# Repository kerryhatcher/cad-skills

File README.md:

# cad-skills

Agent skills for CAD work. You can install them with the [`skills`](https://skills.sh) CLI into Claude Code, Codex, Cursor, OpenCode and [many other agents](https://github.com/vercel-labs/skills/blob/main/docs/agents.md).

## Skills

| Skill | Function |
|---|---|
| [`cadquery`](skills/cadquery/SKILL.md) | Make parametric 3D CAD models in Python with [CadQuery](https://cadquery.readthedocs.io/). It includes parts, sketches, assemblies and export to STEP, STL, 3MF, DXF, SVG and glTF. Its tools examine, measure and render models. Thus the agent can make sure that its work is correct. All Python runs with `uv`. |
| [`structural-analysis`](skills/structural-analysis/SKILL.md) | Find if a part is sufficiently strong for its task. It does a linear static FEA (gmsh and scikit-fem, quadratic tetrahedra) of CadQuery or STEP models. It calculates safety factors with data for **printed** Prusament and Jessie materials. It also examines the layer adhesion for the print orientation. It renders the boundary conditions and the stress to PNG files, and exports VTU files for ParaView. |
| [`print-prep`](skills/print-prep/SKILL.md) | Prepare a model for FDM printing. It examines the mesh. It makes sure that the part is not too large for the build volume. It compares print orientations and puts them in sequence from best to worst. It compares the supports, the area on the bed, the risk that the part falls, and the load across the layers. It also examines the wall thickness and exports the turned model as 3MF or STL. It includes design rules for FDM on the Prusa MK4. |
| [`prusaslicer`](skills/prusaslicer/SKILL.md) | Slice with PrusaSlicer, with no GUI. It uses the Prusa profiles for the MK4 and MK4S, which include Prusament and Jessie filaments. You can change the settings that give strength. It makes sure that the G-code is for the correct printer, nozzle and temperatures. It shows the time, the filament and the slicer warnings. It can read `.bgcode` files. |

For a printed part, use these four skills in this sequence:

1. **Model** the part (`cadquery`).
2. **Turn and examine** the part for printing (`print-prep`).
3. **Calculate the strength** with the same build direction (`structural-analysis`).
4. **Slice** the part (`prusaslicer`).

The repository also contains three PCB skills:

| Skill | Function |
|---|---|
| [`pcb-design`](skills/pcb-design/SKILL.md) | Edit KiCad projects, compare schematic and board identities, run design checks, and measure the supported mechanical fixture. |
| [`pcb-fab-package`](skills/pcb-fab-package/SKILL.md) | Compare fabrication outputs with a supplier profile and make a package with bound evidence. It includes OSH Park setup guidance. |
| [`pcba-design`](skills/pcba-design/SKILL.md) | Apply variants and alternate approvals, make a BOM, compare stock, and make Sierra draft artifacts and an assembly package. |

The KiCad tool operations use a local image whose identity matches the project toolchain lock.
The skill guides state the supported geometry, source setup, commands and qualification limits.
A package with status `unqualified` does not establish supplier acceptance or a physical test result.

## How to install the skills

### Claude Code plugin

This repository is a Claude Code plugin marketplace. It supplies the plugin `cad-skills` with all seven skills.

```
/plugin marketplace add kerryhatcher/cad-skills
/plugin install cad-skills@cad-skills
```

The plugin has a `SessionStart` hook. The hook tells the agent the path of the plugin.
Thus the agent can resolve the script paths, such as `skills/cadquery/scripts/inspect_model.py`, in the skill documents.
The plugin is in `plugins/cad-skills`. Its `skills` link points to the `skills` directory of the repository.

### Other agents

```bash
# this project (select the agents in a menu)
npx skills add kerryhatcher/cad-skills

# one skill, one agent, for all projects
npx skills add kerryhatcher/cad-skills --skill cadquery -a claude-code -g

# show the contents of the repository
npx skills add kerryhatcher/cad-skills --list
```

The computer that runs the agent must have:

- [uv](https://docs.astral.sh/uv/). It downloads CadQuery when necessary. It is not necessary to install CadQuery.
- Node.js (minimum version 22.20), for the `skills` CLI.
- [PrusaSlicer](https://www.prusa3d.com/page/prusaslicer_424/) (minimum version 2.8), for the `prusaslicer` skill only. On Linux: `flatpak install flathub com.prusa3d.PrusaSlicer`.

## Contents of `cadquery`

```
skills/cadquery/
├── SKILL.md                    # procedure, mental model, quick reference, frequent mistakes
├── references/                 # the agent reads these when necessary
│   ├── workplane.md            # fluent API: workplanes, 2D, 3D operations, patterns, tags
│   ├── selectors.md            # selection of faces, edges and vertices
│   ├── sketch.md               # cq.Sketch: profiles from faces, edges or constraints
│   ├── assemblies.md           # Assembly, Location, constraints, colors
│   ├── free-func.md            # cadquery.func, Shape API, Vector/Plane/Location
│   ├── import-export.md        # formats, units, mesh tolerance, imports
│   ├── recipes.md              # 12 tested examples
│   ├── design-guidelines.md    # general rules for FDM, CNC, laser and sheet metal
│   └── troubleshooting.md      # error message → cause → repair
├── scripts/
│   ├── inspect_model.py        # build, validate, measure, export and render PNG views
│   └── cq_api.py               # signatures and docstrings of the installed CadQuery
└── templates/
    ├── part.py                 # start file for a parametric part (PEP 723)
    └── assembly.py             # start file for a parametric assembly (PEP 723)
```

The scripts have [PEP 723](https://peps.python.org/pep-0723/) headers. Thus they run on all computers with `uv run`:

```bash
uv run skills/cadquery/scripts/inspect_model.py my_part.py --png out/preview.png --views -o out/my_part.step
uv run skills/cadquery/scripts/cq_api.py Workplane.cboreHole
```

`inspect_model.py` does these tasks:

- It shows if the model is correct. It also shows the number of solids, the bounding box, the volume and the center of mass.
- It changes top-level parameters (`--set width=50`).
- It finds interference in an assembly (`--interference`).
- It exports to all supported formats (`-o`).
- It renders PNG views (iso, front, top, right) with no screen. An agent that can read images can examine these views.

## Example: from a model to a print

```bash
# 1. orientation and printability (shows the build direction for the FEA)
uv run skills/print-prep/scripts/printability.py bracket.py --load-axis z --png out/orient.png -o out/bracket.3mf
# 2. can the part hold 100 N in this orientation?
uv run skills/structural-analysis/scripts/fea.py bracket.py --material jessie-petg \
    --fix "face:7" --force "face:5=0,0,-100" --build-dir y --sf-target 3 --png out/fea.png
# 3. slice for an MK4 with settings for strength
uv run skills/prusaslicer/scripts/slice.py slice out/bracket.3mf --printer MK4 \
    --filament "Jessie PETG" --perimeters 5 --infill 40% -o out/bracket.bgcode
```

## Tests

The test script runs each ```` ```python ```` code block in the Markdown files of the skills. It uses the CadQuery version that `uv` installs:

```bash
uv run tests/test_snippets.py          # all blocks
uv run tests/test_snippets.py -k recipes -v
```

If a code block cannot run without other code, put `# notest: <reason>` on its first line. A mark with no reason fails the test.

The FEA, printability and slicer tools have regression tests:

- The FEA results agree with beam theory.
- The profile resolution agrees with the Prusa profile bundle.
- If the computer has PrusaSlicer, a test slices a model.

```bash
uv run tests/test_print_tools.py
```

The record contracts in `contracts/` have their own tests:

```bash
uv run tests/test_pcb_tools.py
uv run tests/test_project_io.py
uv run tests/test_skill_packages.py
uv run tests/test_snippets.py --dry-run   # show the environment of each block
```

CI runs these test scripts each time that you push commits (`.github/workflows/test.yml`).

### Language

Write all documentation, code comments, help text, commit messages and agent messages in ASD-STE100 Simplified Technical English (STE). `AGENTS.md` gives the rules and examples. `CLAUDE.md` imports `AGENTS.md` for Claude Code.

## Local release checks

These commands run without a model provider:

```bash
uv run tests/test_release_packaging.py
uv run tests/test_release_harness.py
uv run tests/test_release_isolation.py
uv run tests/test_artifact_fixtures.py
uv run tests/test_artifact_expectations.py
```

The packaging suite examines the source manifests and distribution exclusions.
The harness uses local stubs. The isolation suite measures the supported local filesystem and network boundary.
The artifact suites compare retained fixture results and altered temporary copies with explicit expectations.
These results do not establish the authenticated host route or live-provider behavior.
Provider authorization remains zero. The artifact evaluations remain held.

Supplier pages and documents remain local evidence. Distribution excludes their full copies.
The fabrication skill has a separate source setup command. Its guide states the hash and source-review rules.
See [the licensing record](docs/release-licensing.md) for third-party content and distribution decisions.

## License

MIT

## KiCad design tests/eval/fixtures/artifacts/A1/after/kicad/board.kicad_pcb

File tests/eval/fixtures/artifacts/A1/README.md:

# A1: pcb-design value edit (ready)

This fixture holds an owned copy of the accepted RC bare board. It records one design edit: R2 changes from 10k to 20k.

- `before/`: the accepted template `skills/pcb-design/templates/rc-bare-board`, unchanged.
- `after/`: the same project after the edit. The schematic and the board hold 20k. The interface names the edited board.
- `after/expect/r2-value.json`: the expected difference. The author wrote it before the edit.
- `after/out/`: the measured results of the tool commands. The history folder holds the prior board.
- `after/README.md`: the template README, unchanged. It still states R2 = 10 kohm and 2.086 V. This file states the values for R2 = 20 kohm.
- `after/simulations/`: the simulation circuit and its assertion. Both model R2 = 20k.

Procedure, in order:

1. Write the expected difference before the edit.
2. Change the Value of R2 on line 980 of `kicad/board.kicad_sch`. No other line changes.
3. Run `erc`. It passes with zero findings.
4. Run `update --adapter gui --expect expect/r2-value.json`. It passes on the measured image ID `b2731833711a`.
5. Run `interface --apply`. The tool rebinds the interface to the saved board and writes the hash. The author does not edit the hash.
6. Run `drc`. It passes. Run `erc` again, because the board changed. It passes.
7. Run `sim`. It measures 1.298448 V.
8. Run `check --for ready`. It exits 0 and reports `ready`.

The simulation values differ from the template. The template assertion of 2.086 V belongs to R2 = 10k. For R2 = 20k, the author computed the expected value as 3.3 V times (1 minus e to the power of minus 0.5). The result is 1.29845 V. The assertion is 1.298 V, with the template tolerance of 1 percent (0.01298 V).

The focused test `tests/test_artifact_fixtures.py` checks these facts from the repository files. It starts no container and no KiCad process.

Limits: one measured GUI dialog layout, KiCad 10.0.5, the local image only. No supplier record is bound. No provider call. No real HOME is used.

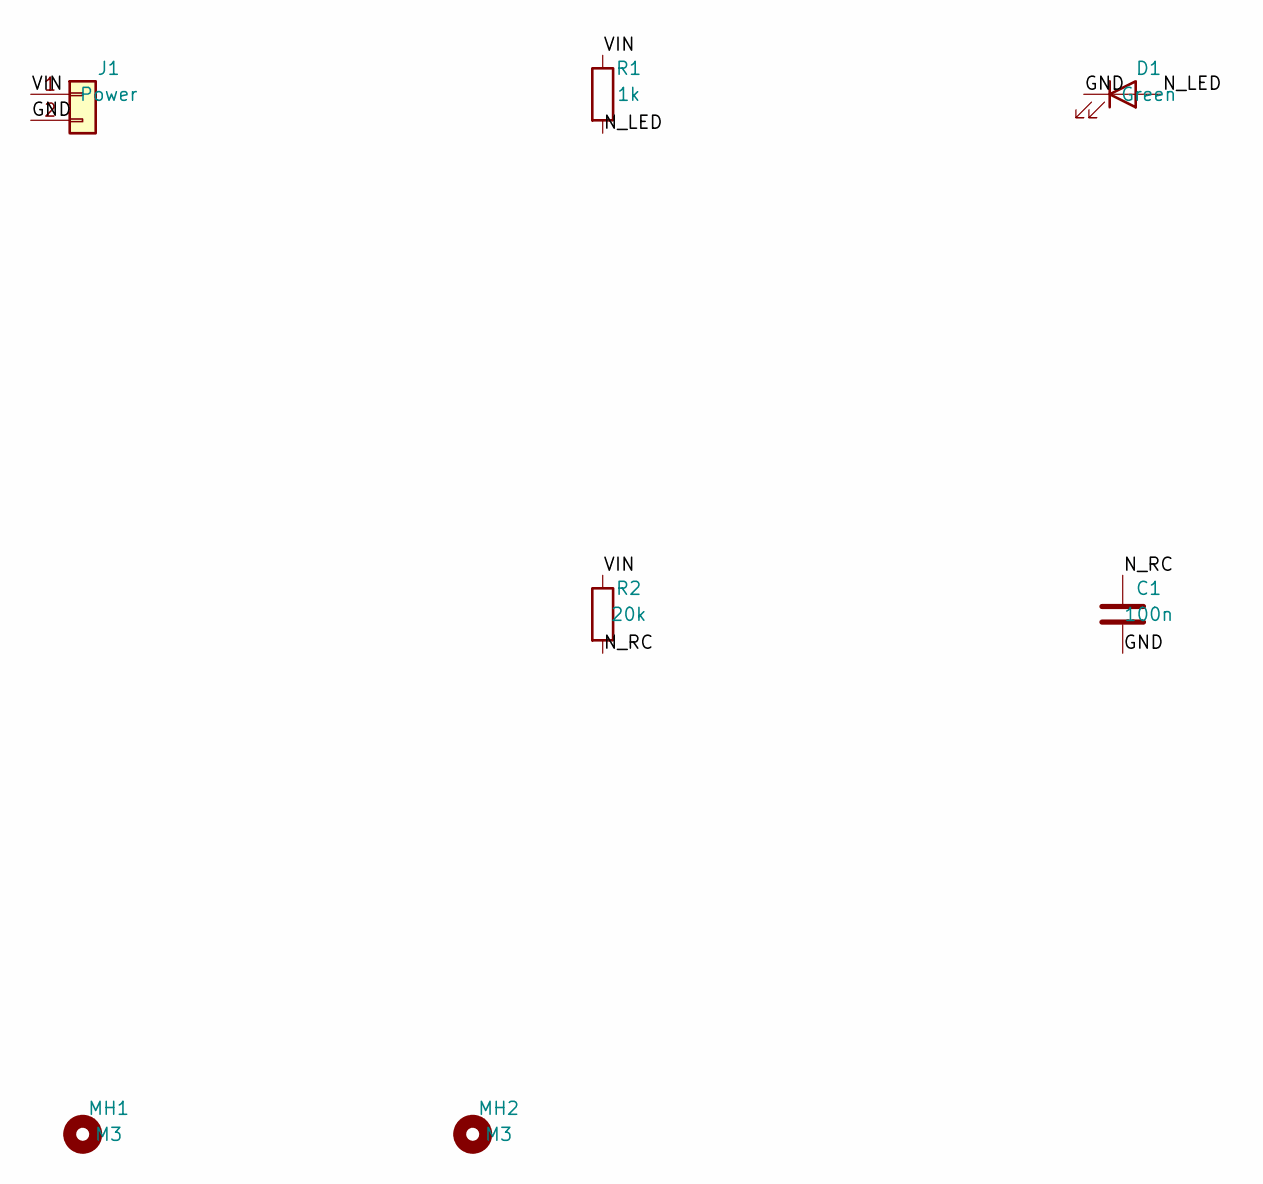
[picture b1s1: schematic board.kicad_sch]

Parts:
C1: 100n; C_0603_1608Metric
D1: Green; LED_0603_1608Metric
J1: Power; PinHeader_1x02_P2.54mm_Vertical
MH1, MH2: M3; MountingHole_3.2mm_M3
R1: 1k; R_0603_1608Metric
R2: 20k; R_0603_1608Metric

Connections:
/GND: C1.2, D1.1 (K), J1.2
/N_LED: D1.2 (A), R1.2
/N_RC: C1.1, R2.2
/VIN: J1.1, R1.1, R2.1

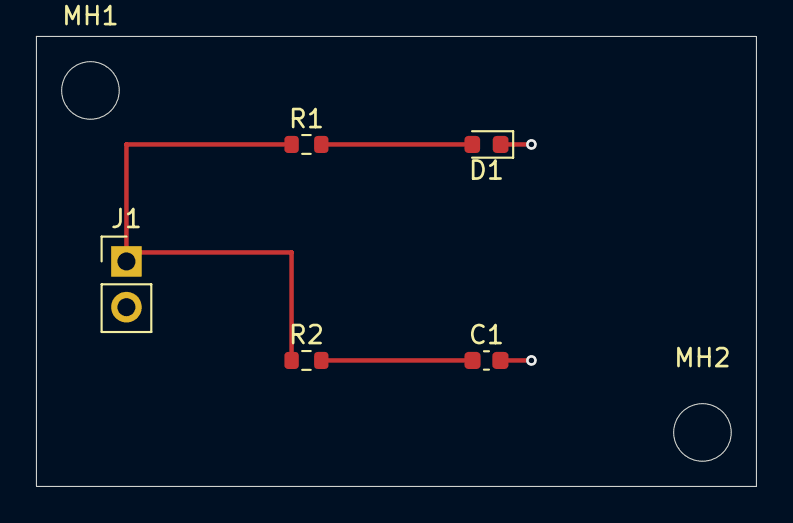
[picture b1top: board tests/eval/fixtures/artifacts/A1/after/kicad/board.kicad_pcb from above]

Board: 2 copper layers, 40.0 x 25.0 mm, 7 parts (0 on the bottom side), 4 nets.

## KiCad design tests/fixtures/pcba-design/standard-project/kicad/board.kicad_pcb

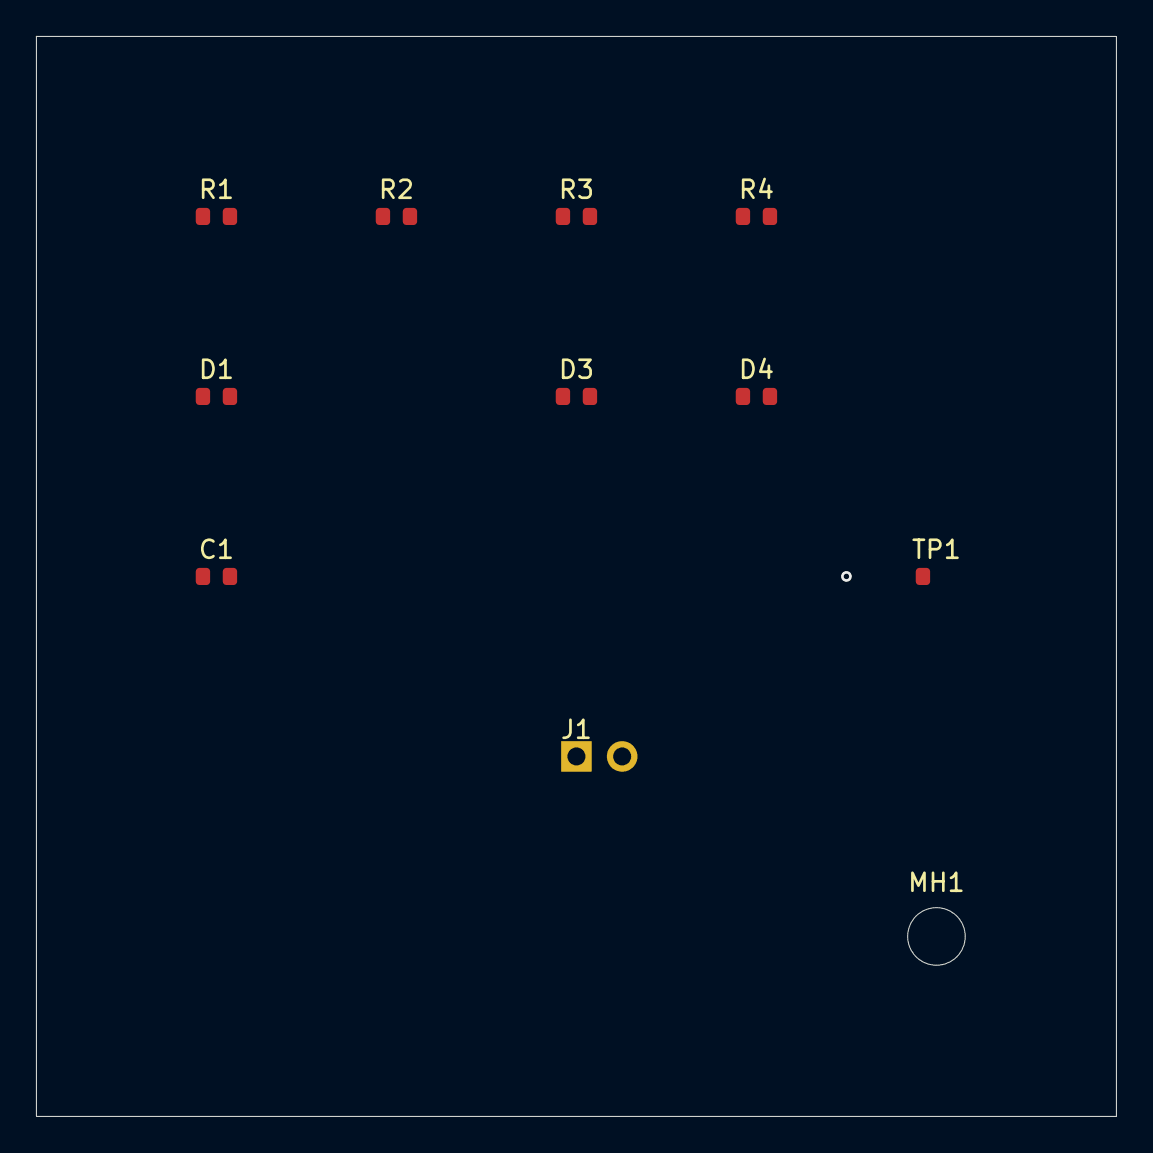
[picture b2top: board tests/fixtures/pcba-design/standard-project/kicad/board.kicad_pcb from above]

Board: 2 copper layers, 60.0 x 60.0 mm, 12 parts (1 on the bottom side), 6 nets, no tracks yet.

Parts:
C1: C1-value; C_0603_1608Metric
D1: D1-value; LED_0603_1608Metric
D2: D2-value; LED_0603_1608Metric
D3: D3-value; LED_0603_1608Metric
D4: D4-value; LED_0603_1608Metric
J1: J1-value; PinHeader_1x02_P2.54mm_Vertical
MH1: MountingHole_3.2mm_M3
R1: R1-value; R_0603_1608Metric
R2: R2-value; R_0603_1608Metric
R3: R3-value; R_0603_1608Metric
R4: R4-value; R_0603_1608Metric
TP1: TP1-value; TestPoint_Pad_D1.0mm

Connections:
GND: C1.2, D1.1, D2.1, D3.1, D4.1, J1.2
N1: D1.2, R1.2
N2: D2.2, R2.2
N3: D3.2, R3.2
N4: D4.2, R4.2
VCC: C1.1, J1.1, R1.1, R2.1, R3.1, R4.1, TP1.1
